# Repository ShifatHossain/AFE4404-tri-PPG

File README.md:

# AFE4404-tri-PPG
An AFE4404 and ESP32 PICO D4/V3 based device to acquire three wavelength PPG signal.

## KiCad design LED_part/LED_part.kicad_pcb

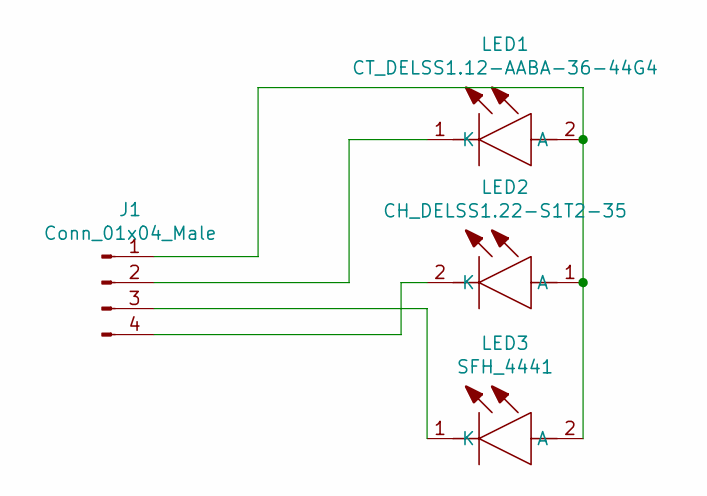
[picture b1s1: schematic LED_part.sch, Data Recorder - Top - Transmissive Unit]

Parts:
J1: Conn_01x04_Male; PinSocket_1x04_P2.54mm_Vertical
LED1: CT_DELSS1.12-AABA-36-44G4; CTDELSS112AABA3644G4; Manufacturer_Part_Number CT DELSS1.12-AABA-36-44G4; Mouser Part Number 720-CTDELSS112A1193
LED2: CH_DELSS1.22-S1T2-35; CHDELSS122S1T235; Manufacturer_Part_Number CH DELSS1.22-S1T2-35; Mouser Part Number 720-CHDELSS122A1192
LED3: SFH_4441; LEDM2320X105N; Manufacturer_Part_Number SFH 4441; Mouser Part Number 720-SFH4441

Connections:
unnamed: J1.1, LED1.2 (A), LED2.1 (A), LED3.2 (A)
unnamed: J1.2, LED1.1 (K)
unnamed: J1.3, LED3.1 (K)
unnamed: J1.4, LED2.2 (K)

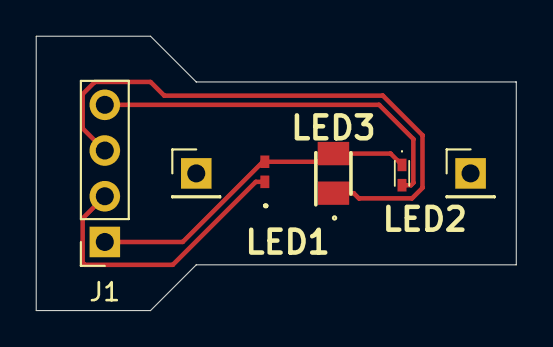
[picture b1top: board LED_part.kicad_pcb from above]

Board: 2 copper layers, 26.7 x 15.2 mm, 4 parts (0 on the bottom side), 4 nets.

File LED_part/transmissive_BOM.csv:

Id,Designator,Package,Quantity,Designation,Supplier and ref
1,"REF**,REF**",PinHeader_1x01_P2.54mm_Vertical,2,PinHeader_1x01_P2.54mm_Vertical,
2,LED3,LEDM2320X105N,1,SFH_4441,
3,LED2,CHDELSS122S1T235,1,CH_DELSS1.22-S1T2-35,
4,LED1,CTDELSS112AABA3644G4,1,CT_DELSS1.12-AABA-36-44G4,
5,J1,PinSocket_1x04_P2.54mm_Vertical,1,Conn_01x04_Male,

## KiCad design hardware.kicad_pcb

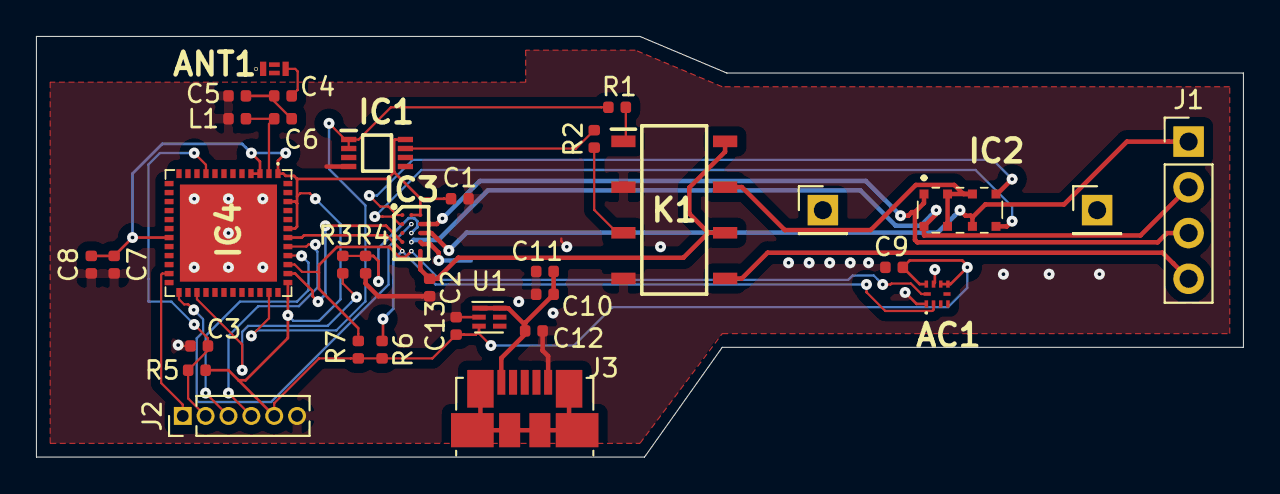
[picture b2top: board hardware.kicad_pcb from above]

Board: 2 copper layers, 67.1 x 23.4 mm, 32 parts (0 on the bottom side), 28 nets.

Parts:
AC1: MC3635
ANT1: ANT016008LCS2442MA1; ANT016008LCD1575MA1
C1, C2, C12, C13: 1uF; C_0402_1005Metric
C3, C8, C9, C10: 0.1uF; C_0402_1005Metric
C4, C5: 2.7pF; C_0402_1005Metric
C6: 4.7pF; C_0402_1005Metric
C7, C11: 10uF; C_0402_1005Metric
IC1: 74AUP2G00DC-Q100H; SOP50P310X100-8N
IC2: SFH_7050; SFH7050
IC3: AFE4404YZPT; BGA15C50P3X5_160X260X50
IC4: ESP32-PICO-D4; ESP32PICOD4
J1: Conn_01x04_Male; PinHeader_1x04_P2.54mm_Vertical
J2: Conn_01x06_Female; PinHeader_1x06_P1.27mm_Vertical
J3: USB_B_Micro; USB_Micro-B_Molex_47346-0001
K1: CPC2030N; SOP254P610X218-8N
L1: 1.6nH; L_0402_1005Metric
R1, R2: 412; R_0402_1005Metric
R3, R4: 499k; R_0402_1005Metric
R5: 10K; R_0402_1005Metric
R6, R7: 4.7k; R_0402_1005Metric
U1: TLV70233_WSON6; WSON-6_1.5x1.5mm_P0.5mm

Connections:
3.3VMCU: AC1.6, AC1.7, AC1.9, C1.1, C7.1, C8.1, C9.1, C13.1, IC1.8, IC3.A2, IC3.A3, IC4.1, IC4.3, IC4.4, IC4.19, IC4.37, IC4.43, IC4.46, J2.5, R5.1, R6.2, R7.2, U1.3
+5V: C2.1, IC3.E3, K1.6, K1.8
GND: AC1.1, AC1.8, C1.2, C2.2, C3.2, C5.2, C7.2, C8.2, C9.2, C10.2, C11.2, C12.2, C13.2, IC1.4, IC3.D3, IC4.49, J2.6, J3.5, K1.2, K1.4, L1.2, R4.1, U1.2
INV_MODE: IC1.7, R2.2
IO0: IC4.23, J2.1
LED_G: IC2.1, IC3.B3, J1.3
LED_IR: IC2.8, IC3.D2, J1.2
LED_R: IC2.6, IC3.C3, J1.1
LNA: C6.1, IC4.2, L1.1
MCU_ADC_RDY: IC3.B2, IC4.25
MCU_CLK: IC4.27, R3.2
MCU_RESETZ: IC3.D1, IC4.38
MODE: IC1.1, IC1.2, IC4.35, R1.2
unnamed: ANT1.3, C4.2
unnamed: C4.1, C5.1, C6.2
unnamed: IC2.4, IC3.A1
unnamed: IC2.5, IC3.B1
unnamed: IC3.C2, R3.1, R4.2
unnamed: K1.1, R1.1
unnamed: K1.3, R2.1
RST: C3.1, IC4.9, J2.2, R5.2
RX: IC4.40, J2.3
R_LED_AN: IC2.2, IC2.3, IC2.7, K1.7
SCL: AC1.10, IC3.E2, IC4.39, R7.1
SDA: AC1.2, IC3.E1, IC4.42, R6.1
TX: IC4.41, J2.4
T_LED_AN: J1.4, K1.5
USBVDD: C10.1, C11.1, C12.1, J3.1, U1.1, U1.6

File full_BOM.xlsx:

Id | Designator | Package | Quantity | Designation
1 | U1 | WSON-6_1.5x1.5mm_P0.5mm | 1 | TLV70233_WSON6
2 | R7,R6 | R_0402_1005Metric | 2 | 4.7k
3 | R5 | R_0402_1005Metric | 1 | 10K
4 | R4,R3 | R_0402_1005Metric | 2 | 499k
5 | R2,R1 | R_0402_1005Metric | 2 | 412
6 | L1 | L_0402_1005Metric | 1 | 1.6nH
7 | K1 | SOP254P610X218-8N | 1 | CPC2030N
8 | J3 | USB_Micro-B_Molex_47346-0001 | 1 | USB_B_Micro
9 | J2 | PinHeader_1x06_P1.27mm_Vertical | 1 | Conn_01x06_Female
10 | IC4 | ESP32PICOD4 | 1 | ESP32-PICO-D4
11 | IC3 | BGA15C50P3X5_160X260X50 | 1 | AFE4404YZPT
12 | IC2 | SFH7050 | 1 | SFH_7050
13 | IC1 | SOP50P310X100-8N | 1 | 74AUP2G00DC-Q100H
14 | C13,C12,C2,C1 | C_0402_1005Metric | 4 | 1uF
15 | C11,C7 | C_0402_1005Metric | 2 | 10uF
16 | C10,C9,C8,C3 | C_0402_1005Metric | 4 | 0.1uF
17 | C6 | C_0402_1005Metric | 1 | 4.7pF
18 | C5,C4 | C_0402_1005Metric | 2 | 2.7pF
19 | ANT1 | ANT016008LCD1575MA1 | 1 | ANT016008LCS2442MA1
20 | AC1 | MC3635 | 1 | MC3635
21 | LED3 | LEDM2320X105N | 1 | SFH_4441
22 | LED2 | CHDELSS122S1T235 | 1 | CH_DELSS1.22-S1T2-35
23 | LED1 | CTDELSS112AABA3644G4 | 1 | CT_DELSS1.12-AABA-36-44G4

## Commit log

2020-08-30 Kicad files
